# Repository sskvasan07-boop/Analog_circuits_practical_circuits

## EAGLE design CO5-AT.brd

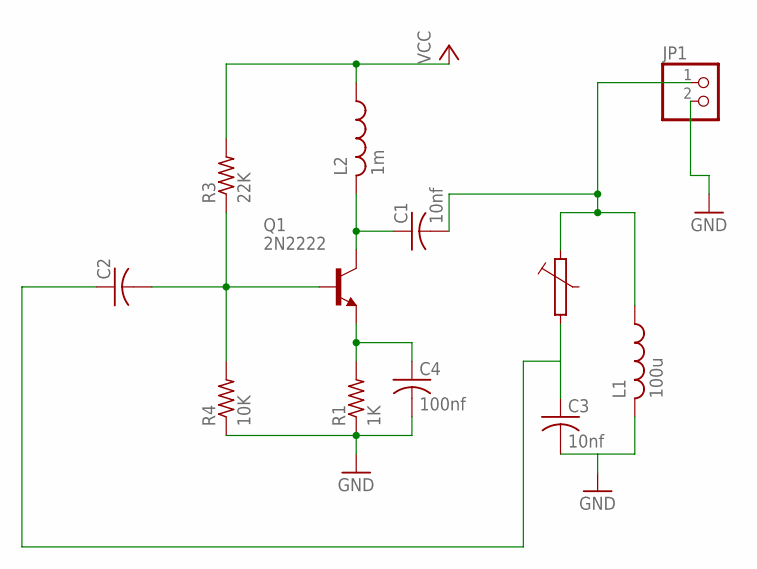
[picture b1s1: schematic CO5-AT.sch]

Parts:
C1, C3: 10nf; C050-025X075
C2: C-US050-025X075; C050-025X075
C4: 100nf; C050-025X075
JP1: PINHD-1X2; 1X02
L1: 100u; 0207/10
L2: 1m; 0207/10
Q1: 2N2222; TO18
R1: 1K; 0207/10
R3: 22K; 0207/10
R4: 10K; 0207/10

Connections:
GND: C4.2, JP1.2, R1.1, R4.1
unnamed: C1.1, L2.2, Q1.3 (C)
unnamed: C4.1, Q1.1 (E), R1.2
unnamed: C2.2, Q1.2 (B), R3.1, R4.2
unnamed: C1.2, JP1.1, L1.1
unnamed: C3.2, L1.2
VCC: L2.1, R3.2

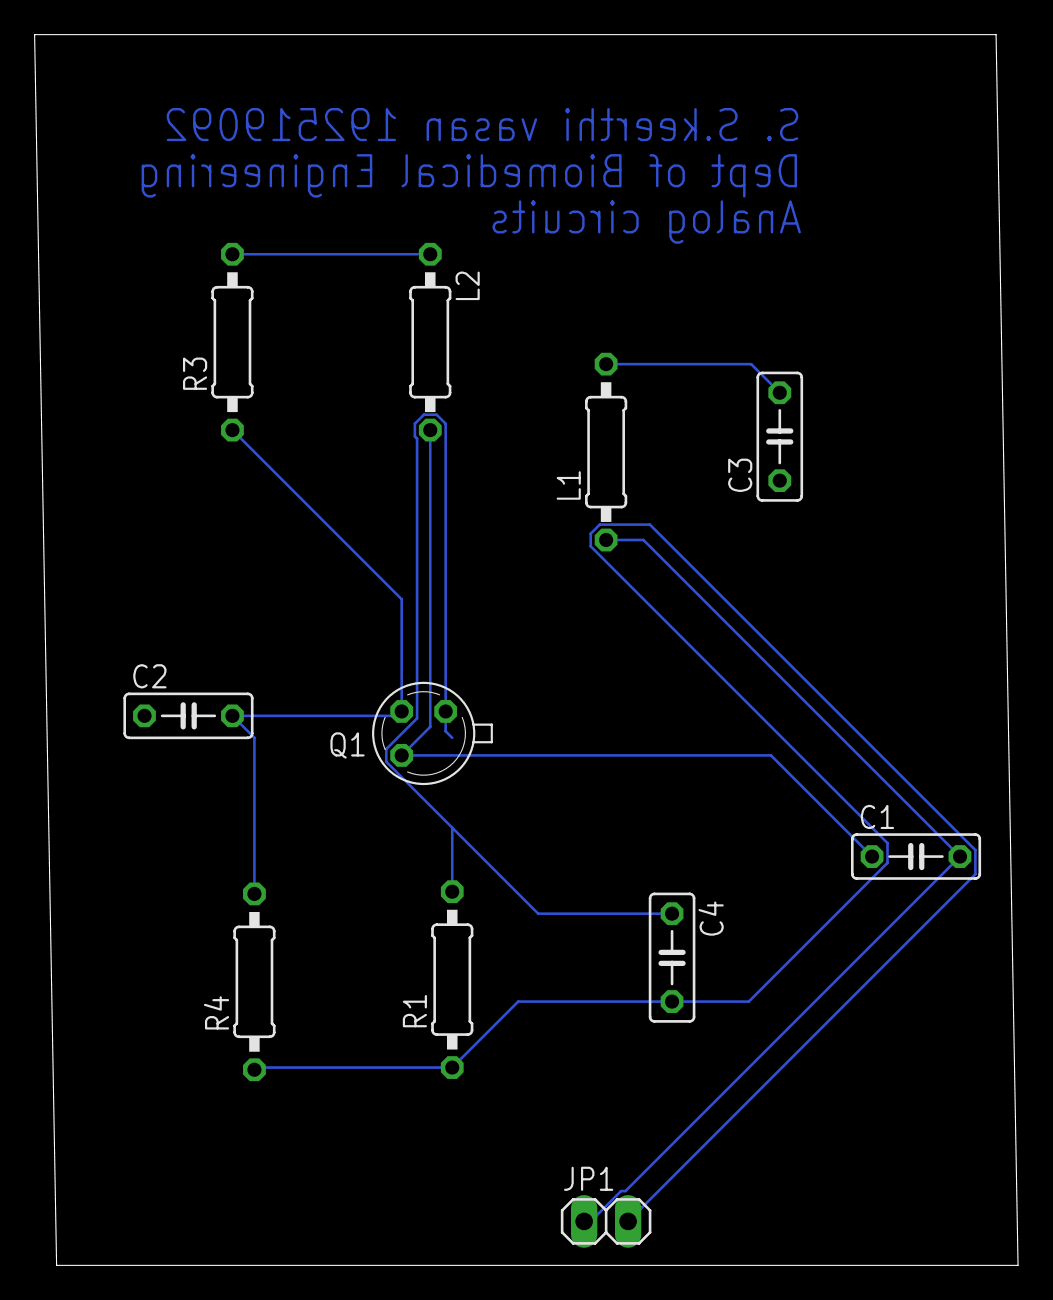
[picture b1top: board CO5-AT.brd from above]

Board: 2 copper layers, 56.8 x 71.1 mm, 11 parts (0 on the bottom side), 7 nets.
